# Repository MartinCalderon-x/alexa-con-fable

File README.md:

# Satélite de voz r1

Una placa electrónica para un asistente de voz, diseñada con Claude Fable 5.2 a partir de un pedido
corto y verificada en cada paso con herramientas libres.

**Estado: prototipo sin fabricar ni medir.** Las verificaciones de este repositorio comprueban reglas
de dibujo y una simulación con modelos simplificados. No validan el comportamiento eléctrico, térmico,
acústico ni de radio de una placa real.

## Qué es

| | |
|---|---|
| Placa | Redonda, 62 mm, 2 capas, 28 componentes |
| Procesador | ESP32-S3-WROOM-1 (Wi-Fi, USB nativo) |
| Audio | Micrófono digital ICS-43434 y amplificador MAX98357A, cada uno en su bus I2S |
| Estado | LED WS2812B con adaptación de nivel a 5 V |
| Alimentación | USB-C, fusible rearmable de 1 A, regulador AP2112K a 3,3 V |

## Cómo se hizo

1. **Pedido.** Qué dispositivo y qué tipo de componentes: [docs/prompt.md](docs/prompt.md).
2. **Diseño como código.** El modelo escribe componentes, redes y pines en [hardware/design.py](hardware/design.py).
3. **Esquema.** `gen_sch.py` genera el esquemático de KiCad y KiCad revisa las conexiones (ERC).
4. **Banco eléctrico.** `qa/check_power.py` exporta ese mismo esquemático a SPICE y simula la alimentación
   contra límites escritos antes de correr ([hardware/qa/spec.json](hardware/qa/spec.json)).
5. **Placa.** `gen_pcb.py` coloca los componentes, Freerouting traza las pistas y KiCad revisa las reglas (DRC).
6. **Fabricación.** Gerbers, taladros, lista de componentes, posiciones y modelo 3D en [out/fabricacion](out/fabricacion).

Cuando una verificación falla, se corrige el diseño y se regenera todo. Las decisiones y lo que cambió
en el camino están en [docs/DISENO.md](docs/DISENO.md).

## Resultados

| Verificación | Resultado |
|---|---|
| Esquema (ERC) | 0 errores, 1 aviso de biblioteca |
| Placa (DRC) | 0 infracciones, 0 conexiones pendientes, coincide con el esquema |
| Banco eléctrico | 5 casos pasan; 2 casos defectuosos fallan como deben |

El banco encontró dos cosas para atender antes de fabricar ([informe completo](docs/banco-electrico-report.json)):

- Con parlante de 8 Ω a potencia máxima y Wi-Fi transmitiendo, el consumo medio es 0,62 A: más que los
  0,5 A de un puerto USB 2.0. Hace falta una fuente de 1 A o limitar el volumen en el firmware.
- El regulador disipa 0,56 W durante cada ráfaga de Wi-Fi. Con transmisión sostenida hay que medir su temperatura.

## Abrir y regenerar

Abrir `hardware/satelite_voz.kicad_pro` con KiCad 10.

```bash
hardware/build.sh
```

```bash
python3 hardware/export.py fabrication
```

Requisitos y límites de esta versión:

- macOS con KiCad 10 en `/Applications` (las tablas de bibliotecas usan esa ruta).
- `hardware/route.py` busca Freerouting 2.5.0 y su Java en `~/repos/physical-ai/tools/freerouting`.
- `hardware/qa/check_power.py` usa ngspice 47 y las utilidades `spice_lab.py` de un laboratorio propio
  que todavía no es público; sin ellas, el banco no corre.
- Los modelos de `hardware/qa/models` son equivalentes propios y simplificados, no los del fabricante.

## Antes de fabricar

La lista completa está en [docs/DISENO.md](docs/DISENO.md). Lo principal: revisión humana contra las hojas
de datos, alcance de la antena, temperatura del regulador, corriente por USB y el agujero acústico del micrófono.

## Licencia

El diseño de la placa, los archivos de fabricación y los scripts se publican bajo
[CERN-OHL-P v2](LICENSE) (hardware abierto, permisiva). Puedes usarla, modificarla y fabricarla
citando el origen. Se entrega tal cual, sin garantías: es un prototipo que nadie fabricó ni midió.

Fuente: https://github.com/MartinCalderon-x/alexa-con-fable

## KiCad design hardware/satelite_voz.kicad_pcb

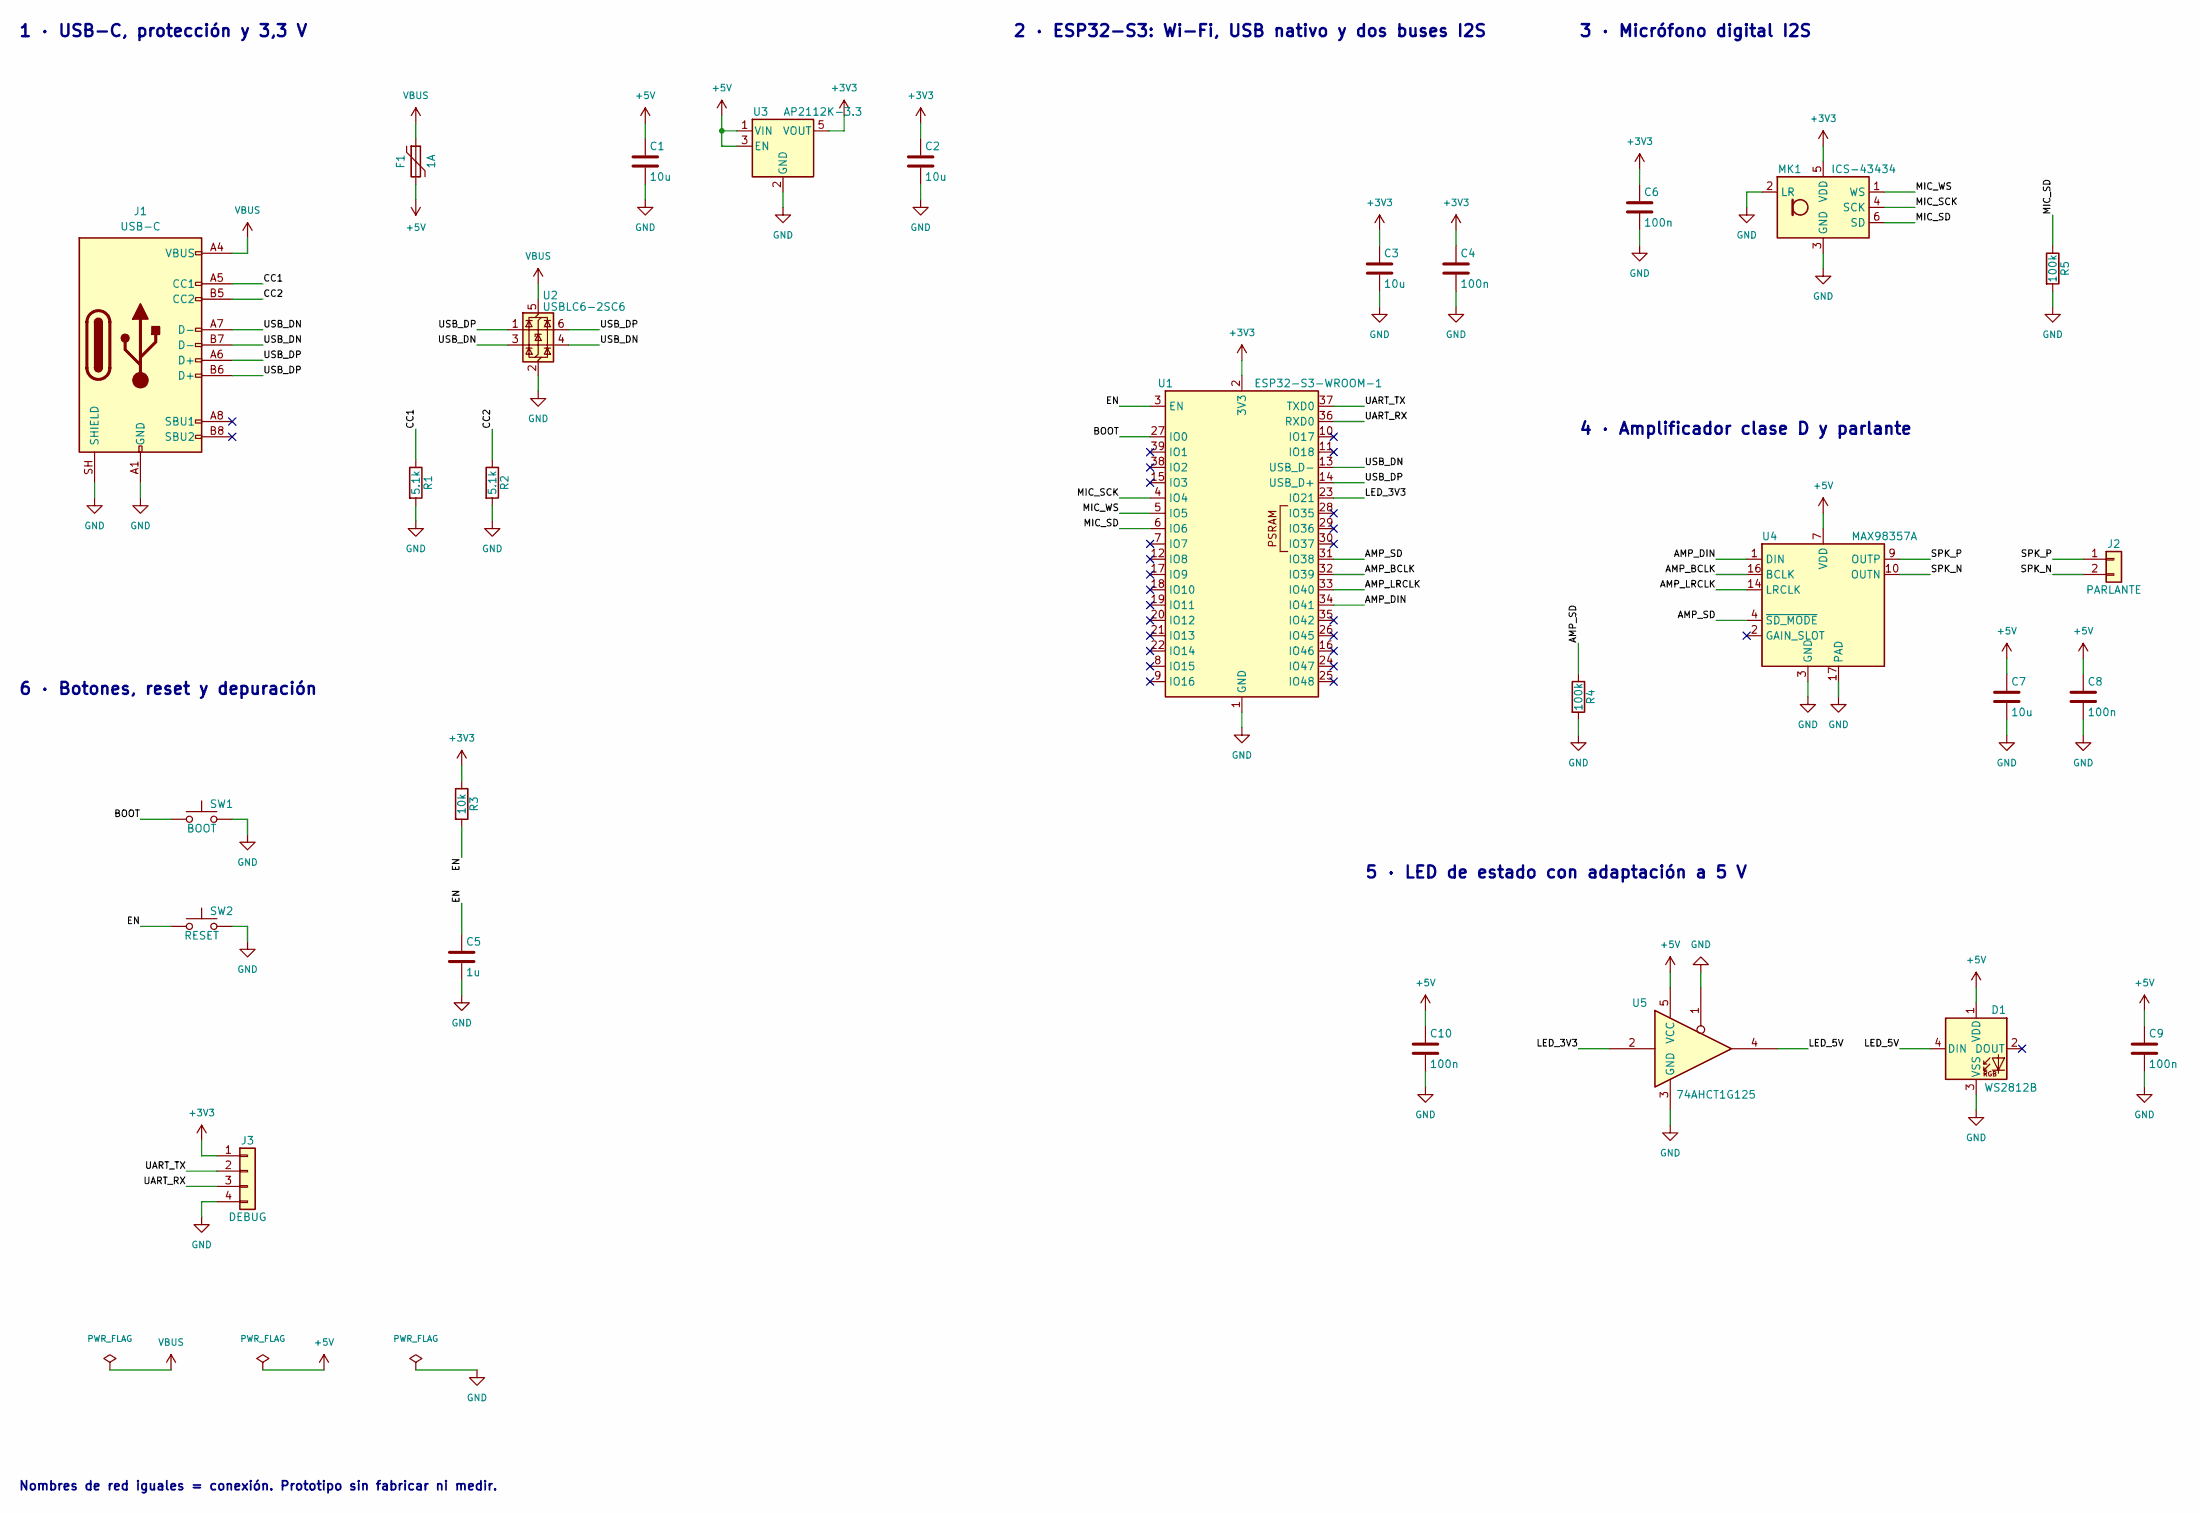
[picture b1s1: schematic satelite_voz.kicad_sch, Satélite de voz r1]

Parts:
C1, C2, C3, C7: 10u; C_0805_2012Metric; MPN Murata GRM21BR61A106KE19L
C4, C6, C8, C9, C10: 100n; C_0603_1608Metric; MPN Murata GRM188R71E104KA01D
C5: 1u; C_0603_1608Metric; MPN Murata GRM188R71C105KA12D
D1: WS2812B; LED_WS2812B_PLCC4_5.0x5.0mm_P3.2mm; MPN Worldsemi WS2812B
F1: 1A; Fuse_1206_3216Metric; MPN Littelfuse 1206L100THYR
J1: USB-C; USB_C_Receptacle_GCT_USB4105-xx-A_16P_TopMnt_Horizontal; MPN GCT USB4105-GF-A
J2: PARLANTE; JST_PH_S2B-PH-K_1x02_P2.00mm_Horizontal; MPN JST S2B-PH-K-S
J3: DEBUG; PinHeader_1x04_P2.54mm_Vertical; MPN Harwin M20-9990446
MK1: ICS-43434; InvenSense_ICS-43434-6_3.5x2.65mm; MPN TDK InvenSense ICS-43434
R1, R2: 5.1k; R_0603_1608Metric; MPN YAGEO RC0603FR-075K1L
R3: 10k; R_0603_1608Metric; MPN YAGEO RC0603FR-0710KL
R4, R5: 100k; R_0603_1608Metric; MPN YAGEO RC0603FR-07100KL
SW1: BOOT; SW_SPST_PTS810; MPN C&K PTS810SJM250SMTRLFS
SW2: RESET; SW_SPST_PTS810; MPN C&K PTS810SJM250SMTRLFS
U1: ESP32-S3-WROOM-1; MPN Espressif ESP32-S3-WROOM-1-N8R2
U2: USBLC6-2SC6; SOT-23-6; MPN ST USBLC6-2SC6
U3: AP2112K-3.3; SOT-23-5; MPN Diodes Inc AP2112K-3.3TRG1
U4: MAX98357A; TQFN-16-1EP_3x3mm_P0.5mm_EP1.23x1.23mm; MPN Analog Devices MAX98357AETE+T
U5: 74AHCT1G125; SOT-23-5; MPN TI SN74AHCT1G125DBVR

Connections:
+3V3: C2.1, C3.1, C4.1, C6.1, J3.1, MK1.5 (VDD), R3.1, U1.2 (3V3), U3.5 (VOUT)
+5V: C1.1, C7.1, C8.1, C9.1, C10.1, D1.1 (VDD), F1.2, U3.1 (VIN), U3.3 (EN), U4.7 (VDD), U4.8 (VDD), U5.5 (VCC)
/AMP_BCLK: U1.32 (IO39), U4.16 (BCLK)
/AMP_DIN: U1.34 (IO41), U4.1 (DIN)
/AMP_LRCLK: U1.33 (IO40), U4.14 (LRCLK)
/AMP_SD: R4.1, U1.31 (IO38), U4.4 (~SD_MODE)
/BOOT: SW1.1, U1.27 (IO0)
/CC1: J1.A5 (CC1), R1.1
/CC2: J1.B5 (CC2), R2.1
/EN: C5.1, R3.2, SW2.1, U1.3 (EN)
/LED_3V3: U1.23 (IO21), U5.2
/LED_5V: D1.4 (DIN), U5.4
/MIC_SCK: MK1.4 (SCK), U1.4 (IO4)
/MIC_SD: MK1.6 (SD), R5.1, U1.6 (IO6)
/MIC_WS: MK1.1 (WS), U1.5 (IO5)
/SPK_N: J2.2, U4.10 (OUTN)
/SPK_P: J2.1, U4.9 (OUTP)
/UART_RX: J3.3, U1.36 (RXD0)
/UART_TX: J3.2, U1.37 (TXD0)
/USB_DN: J1.A7 (D-), J1.B7 (D-), U1.13 (USB_D-), U2.3 (I/O2), U2.4 (I/O2)
/USB_DP: J1.A6 (D+), J1.B6 (D+), U1.14 (USB_D+), U2.1 (I/O1), U2.6 (I/O1)
GND: C1.2, C2.2, C3.2, C4.2, C5.2, C6.2, C7.2, C8.2, C9.2, C10.2, D1.3 (VSS), J1.A1 (GND), J1.A12 (GND), J1.B1 (GND), J1.B12 (GND), J1.SH (SHIELD), J3.4, MK1.2 (LR), MK1.3 (GND), R1.2, R2.2, R4.2, R5.2, SW1.2, SW2.2, U1.1 (GND), U1.40 (GND), U1.41 (GND), U2.2 (GND), U3.2 (GND), U4.3 (GND), U4.11 (GND), U4.15 (GND), U4.17 (PAD), U5.1, U5.3 (GND)
VBUS: F1.1, J1.A4 (VBUS), J1.A9 (VBUS), J1.B4 (VBUS), J1.B9 (VBUS), U2.5 (VBUS)

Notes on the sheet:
1 · USB-C, protección y 3,3 V
2 · ESP32-S3: Wi-Fi, USB nativo y dos buses I2S
3 · Micrófono digital I2S
4 · Amplificador clase D y parlante
5 · LED de estado con adaptación a 5 V
6 · Botones, reset y depuración
Nombres de red iguales = conexión. Prototipo sin fabricar ni medir.

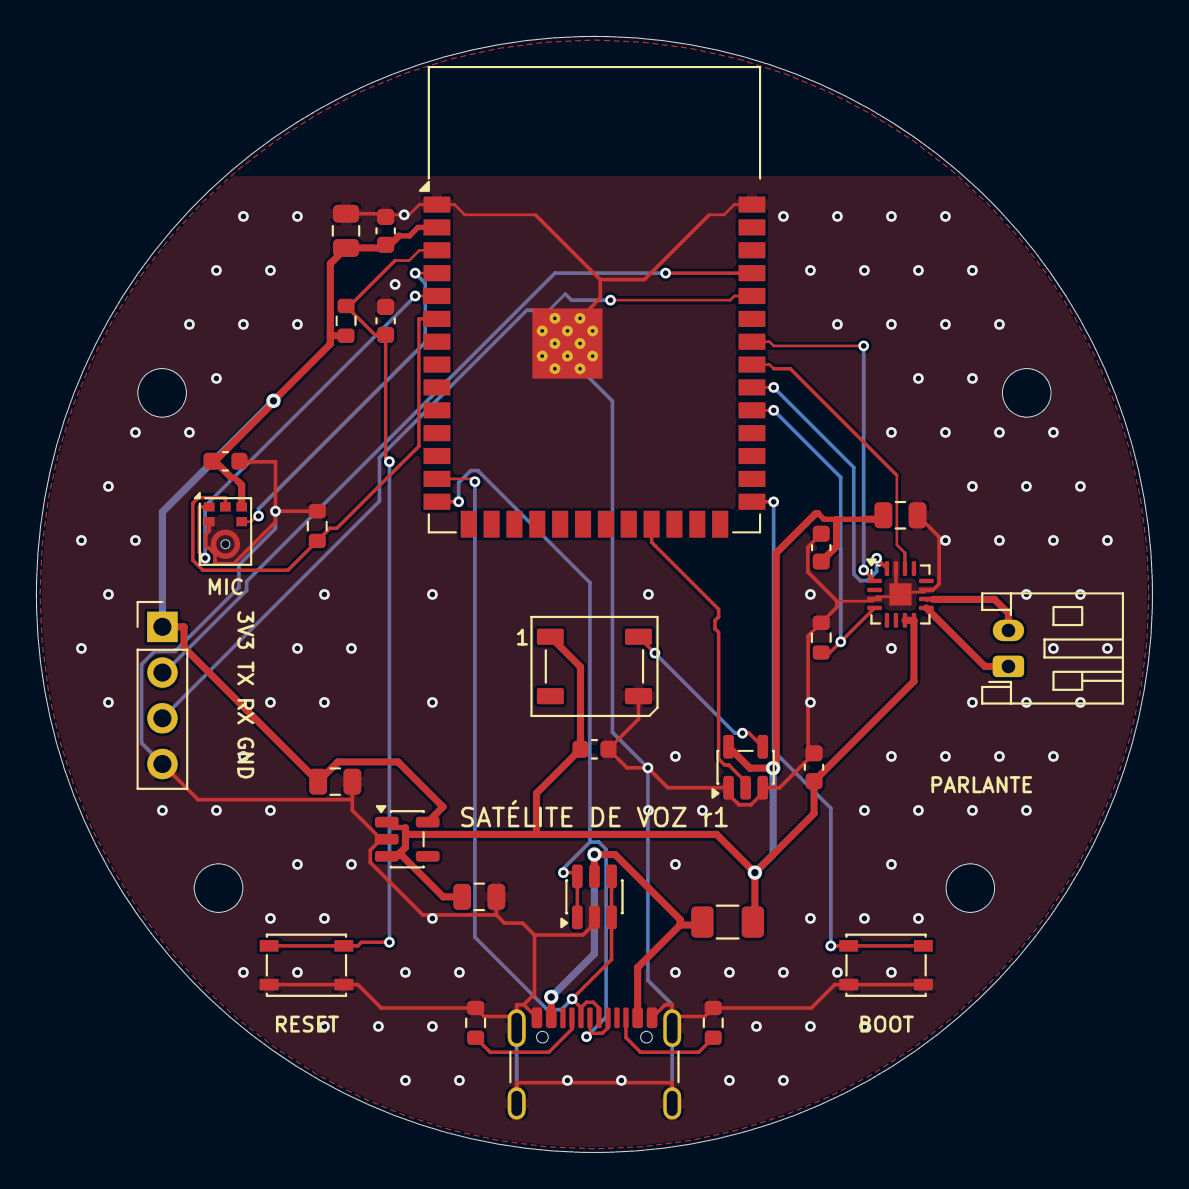
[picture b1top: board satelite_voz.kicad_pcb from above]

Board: 2 copper layers, 62.0 x 62.0 mm, 32 parts (0 on the bottom side), 23 nets.

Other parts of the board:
H1, H2, H3, H4: MountingHole_2.7mm_M2.5

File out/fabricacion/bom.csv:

"Refs","Valor","Huella","MPN","Cant"
"C1-C3,C7","10u","Capacitor_SMD:C_0805_2012Metric","Murata GRM21BR61A106KE19L","4"
"C4,C6,C8-C10","100n","Capacitor_SMD:C_0603_1608Metric","Murata GRM188R71E104KA01D","5"
"C5","1u","Capacitor_SMD:C_0603_1608Metric","Murata GRM188R71C105KA12D","1"
"D1","WS2812B","LED_SMD:LED_WS2812B_PLCC4_5.0x5.0mm_P3.2mm","Worldsemi WS2812B","1"
"F1","1A","Fuse:Fuse_1206_3216Metric","Littelfuse 1206L100THYR","1"
"J1","USB-C","Connector_USB:USB_C_Receptacle_GCT_USB4105-xx-A_16P_TopMnt_Horizontal","GCT USB4105-GF-A","1"
"J2","PARLANTE","Connector_JST:JST_PH_S2B-PH-K_1x02_P2.00mm_Horizontal","JST S2B-PH-K-S","1"
"J3","DEBUG","Connector_PinHeader_2.54mm:PinHeader_1x04_P2.54mm_Vertical","Harwin M20-9990446","1"
"MK1","ICS-43434","Sensor_Audio:InvenSense_ICS-43434-6_3.5x2.65mm","TDK InvenSense ICS-43434","1"
"R1,R2","5.1k","Resistor_SMD:R_0603_1608Metric","YAGEO RC0603FR-075K1L","2"
"R3","10k","Resistor_SMD:R_0603_1608Metric","YAGEO RC0603FR-0710KL","1"
"R4,R5","100k","Resistor_SMD:R_0603_1608Metric","YAGEO RC0603FR-07100KL","2"
"SW1","BOOT","Button_Switch_SMD:SW_SPST_PTS810","C&K PTS810SJM250SMTRLFS","1"
"SW2","RESET","Button_Switch_SMD:SW_SPST_PTS810","C&K PTS810SJM250SMTRLFS","1"
"U1","ESP32-S3-WROOM-1","RF_Module:ESP32-S3-WROOM-1","Espressif ESP32-S3-WROOM-1-N8R2","1"
"U2","USBLC6-2SC6","Package_TO_SOT_SMD:SOT-23-6","ST USBLC6-2SC6","1"
"U3","AP2112K-3.3","Package_TO_SOT_SMD:SOT-23-5","Diodes Inc AP2112K-3.3TRG1","1"
"U4","MAX98357A","Package_DFN_QFN:TQFN-16-1EP_3x3mm_P0.5mm_EP1.23x1.23mm","Analog Devices MAX98357AETE+T","1"
"U5","74AHCT1G125","Package_TO_SOT_SMD:SOT-23-5","TI SN74AHCT1G125DBVR","1"
